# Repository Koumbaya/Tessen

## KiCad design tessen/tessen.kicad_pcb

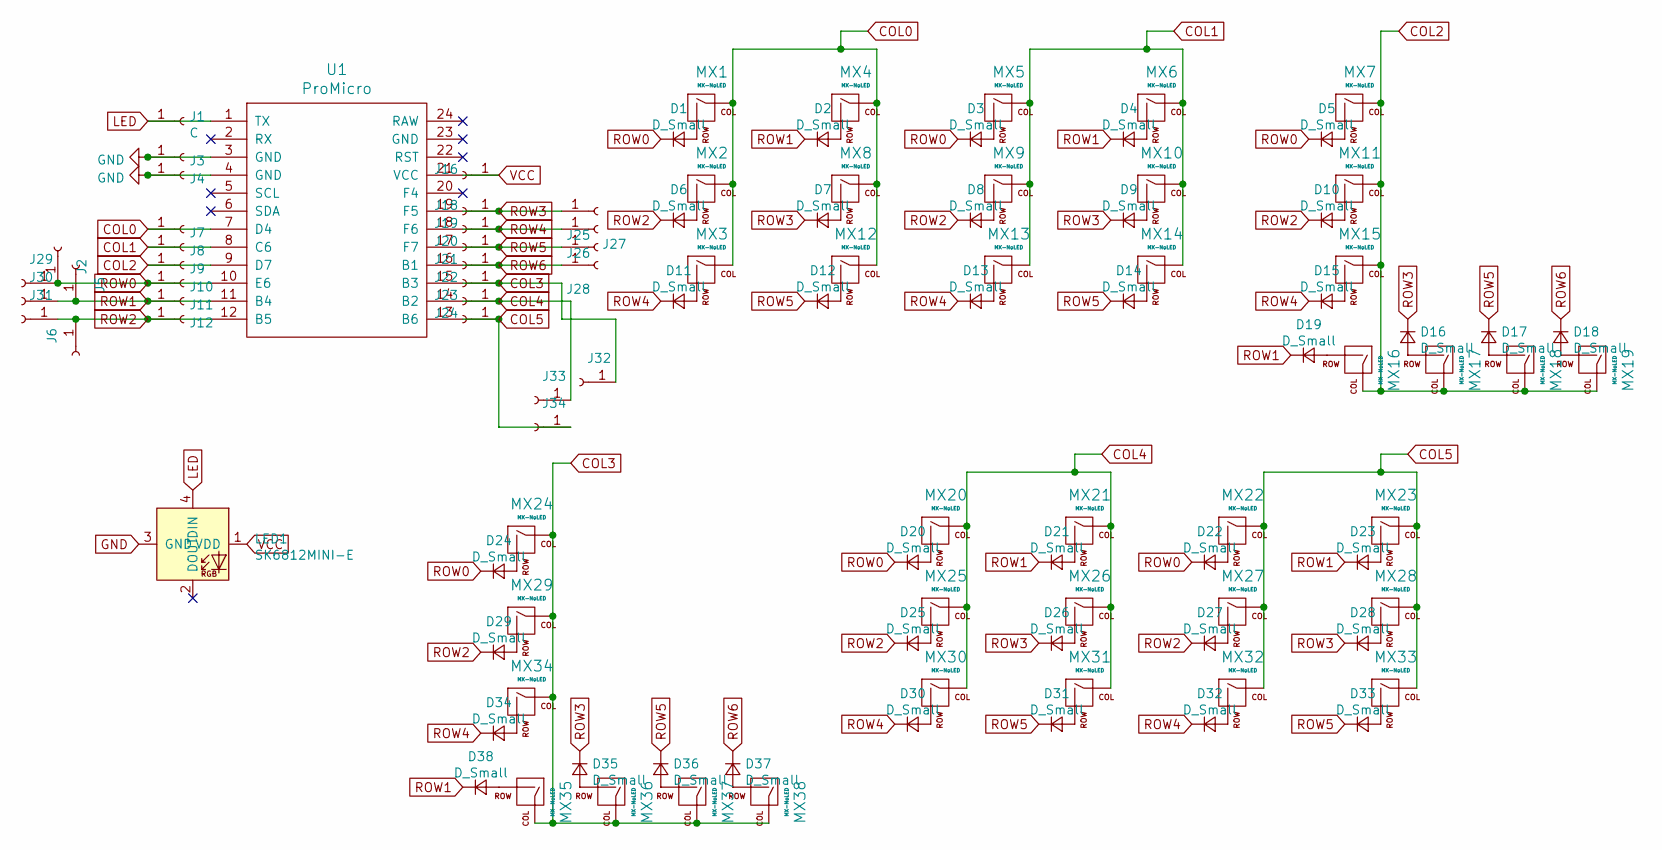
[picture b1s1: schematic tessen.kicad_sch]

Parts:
D1, D2, D3, D4, D5, D6, D7, D8, D9, D10, D11, D12, D13, D14, D15, D16, D17, D18, D19, D20, D21, D22, D23, D24, D25, D26, D27, D28, D29, D30, D31, D32, D33, D34, D35, D36, D37, D38: D_Small; D3_TH_SMD
J1, J2, J3, J4, J5, J6, J7, J8, J9, J10, J11, J12, J25, J26, J27, J28, J29, J30, J31, J32, J33, J34: C; TestPoint_THTPad_2.0x2.0mm_Drill1.0mm
J16, J18, J19, J20, J21, J22, J23, J24: C; TestPoint_THTPad_1.5x1.5mm_Drill0.7mm
LED1: SK6812MINI-E; YS-SK6812MINI-E
MX1, MX2, MX3, MX4, MX5, MX6, MX7, MX8, MX9, MX10, MX11, MX12, MX13, MX14, MX15, MX16, MX17, MX18, MX19, MX20, MX21, MX22, MX23, MX24, MX25, MX26, MX27, MX28, MX29, MX30, MX31, MX32, MX33, MX34, MX35, MX36, MX37, MX38: MX-NoLED; MXOnly-1U-NoLED
U1: ProMicro

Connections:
COL0: J7.1, MX1.1 (COL), MX2.1 (COL), MX3.1 (COL), MX4.1 (COL), MX8.1 (COL), MX12.1 (COL), U1.7 (D4)
COL1: J8.1, MX5.1 (COL), MX6.1 (COL), MX9.1 (COL), MX10.1 (COL), MX13.1 (COL), MX14.1 (COL), U1.8 (C6)
COL2: J9.1, MX7.1 (COL), MX11.1 (COL), MX15.1 (COL), MX16.1 (COL), MX17.1 (COL), MX18.1 (COL), MX19.1 (COL), U1.9 (D7)
COL3: J22.1, J32.1, MX24.1 (COL), MX29.1 (COL), MX34.1 (COL), MX35.1 (COL), MX36.1 (COL), MX37.1 (COL), MX38.1 (COL), U1.15 (B3)
COL4: J23.1, J33.1, MX20.1 (COL), MX21.1 (COL), MX25.1 (COL), MX26.1 (COL), MX30.1 (COL), MX31.1 (COL), U1.14 (B2)
COL5: J24.1, J34.1, MX22.1 (COL), MX23.1 (COL), MX27.1 (COL), MX28.1 (COL), MX32.1 (COL), MX33.1 (COL), U1.13 (B6)
GND: J3.1, J4.1, LED1.3 (GND), U1.3 (GND), U1.4 (GND)
LED: J1.1, LED1.4 (DIN), U1.1 (TX)
unnamed: D1.2 (A), MX1.2 (ROW)
unnamed: D2.2 (A), MX4.2 (ROW)
unnamed: D3.2 (A), MX5.2 (ROW)
unnamed: D4.2 (A), MX6.2 (ROW)
unnamed: D5.2 (A), MX7.2 (ROW)
unnamed: D6.2 (A), MX2.2 (ROW)
unnamed: D7.2 (A), MX8.2 (ROW)
unnamed: D8.2 (A), MX9.2 (ROW)
unnamed: D9.2 (A), MX10.2 (ROW)
unnamed: D10.2 (A), MX11.2 (ROW)
unnamed: D11.2 (A), MX3.2 (ROW)
unnamed: D12.2 (A), MX12.2 (ROW)
unnamed: D13.2 (A), MX13.2 (ROW)
unnamed: D14.2 (A), MX14.2 (ROW)
unnamed: D15.2 (A), MX15.2 (ROW)
unnamed: D16.2 (A), MX17.2 (ROW)
unnamed: D17.2 (A), MX18.2 (ROW)
unnamed: D18.2 (A), MX19.2 (ROW)
unnamed: D19.2 (A), MX16.2 (ROW)
unnamed: D20.2 (A), MX20.2 (ROW)
unnamed: D21.2 (A), MX21.2 (ROW)
unnamed: D22.2 (A), MX22.2 (ROW)
unnamed: D23.2 (A), MX23.2 (ROW)
unnamed: D24.2 (A), MX24.2 (ROW)
unnamed: D25.2 (A), MX25.2 (ROW)
unnamed: D26.2 (A), MX26.2 (ROW)
unnamed: D27.2 (A), MX27.2 (ROW)
unnamed: D28.2 (A), MX28.2 (ROW)
unnamed: D29.2 (A), MX29.2 (ROW)
unnamed: D30.2 (A), MX30.2 (ROW)
unnamed: D31.2 (A), MX31.2 (ROW)
unnamed: D32.2 (A), MX32.2 (ROW)
unnamed: D33.2 (A), MX33.2 (ROW)
unnamed: D34.2 (A), MX34.2 (ROW)
unnamed: D35.2 (A), MX36.2 (ROW)
unnamed: D36.2 (A), MX37.2 (ROW)
unnamed: D37.2 (A), MX38.2 (ROW)
unnamed: D38.2 (A), MX35.2 (ROW)
ROW0: D1.1 (K), D3.1 (K), D5.1 (K), D20.1 (K), D22.1 (K), D24.1 (K), J2.1, J10.1, J29.1, U1.10 (E6)
ROW1: D2.1 (K), D4.1 (K), D19.1 (K), D21.1 (K), D23.1 (K), D38.1 (K), J5.1, J11.1, J30.1, U1.11 (B4)
ROW2: D6.1 (K), D8.1 (K), D10.1 (K), D25.1 (K), D27.1 (K), D29.1 (K), J6.1, J12.1, J31.1, U1.12 (B5)
ROW3: D7.1 (K), D9.1 (K), D16.1 (K), D26.1 (K), D28.1 (K), D35.1 (K), J18.1, J25.1, U1.19 (F5)
ROW4: D11.1 (K), D13.1 (K), D15.1 (K), D30.1 (K), D32.1 (K), D34.1 (K), J19.1, J26.1, U1.18 (F6)
ROW5: D12.1 (K), D14.1 (K), D17.1 (K), D31.1 (K), D33.1 (K), D36.1 (K), J20.1, J27.1, U1.17 (F7)
ROW6: D18.1 (K), D37.1 (K), J21.1, J28.1, U1.16 (B1)
VCC: J16.1, LED1.1 (VDD), U1.21 (VCC)

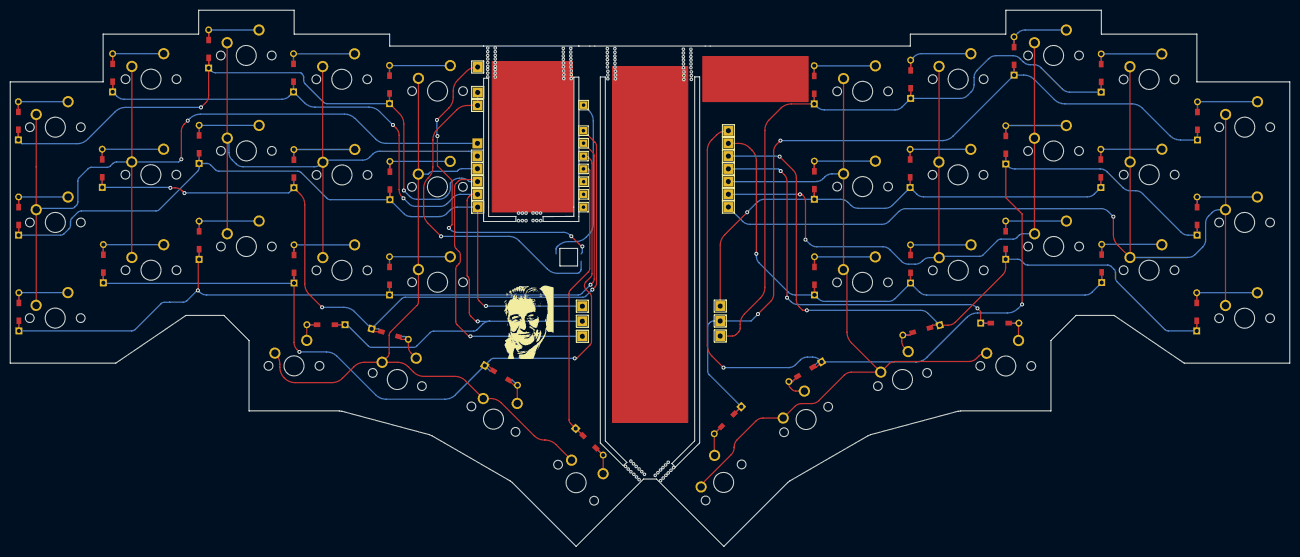
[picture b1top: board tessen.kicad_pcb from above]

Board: 2 copper layers, 255.2 x 106.9 mm, 125 parts (1 on the bottom side), 54 nets.

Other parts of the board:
mouse-bite-2mm-slot, mouse-bite-2mm-slot#2, mouse-bite-2mm-slot#3, mouse-bite-2mm-slot#4, mouse-bite-2mm-slot#5, mouse-bite-2mm-slot#6, mouse-bite-2mm-slot#7, mouse-bite-2mm-slot#8, mouse-bite-2mm-slot#9, mouse-bite-2mm-slot#10, mouse-bite-2mm-slot#11, mouse-bite-2mm-slot#12, mouse-bite-2mm-slot#13, mouse-bite-2mm-slot#14, mouse-bite-2mm-slot#15, mouse-bite-2mm-slot#16, mouse-bite-2mm-slot#17, mouse-bite-2mm-slot#18: VAL**; mouse-bite-2mm-slot

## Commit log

2021-06-15 first commit, not yet ready
2021-06-16 add other kicad projects
